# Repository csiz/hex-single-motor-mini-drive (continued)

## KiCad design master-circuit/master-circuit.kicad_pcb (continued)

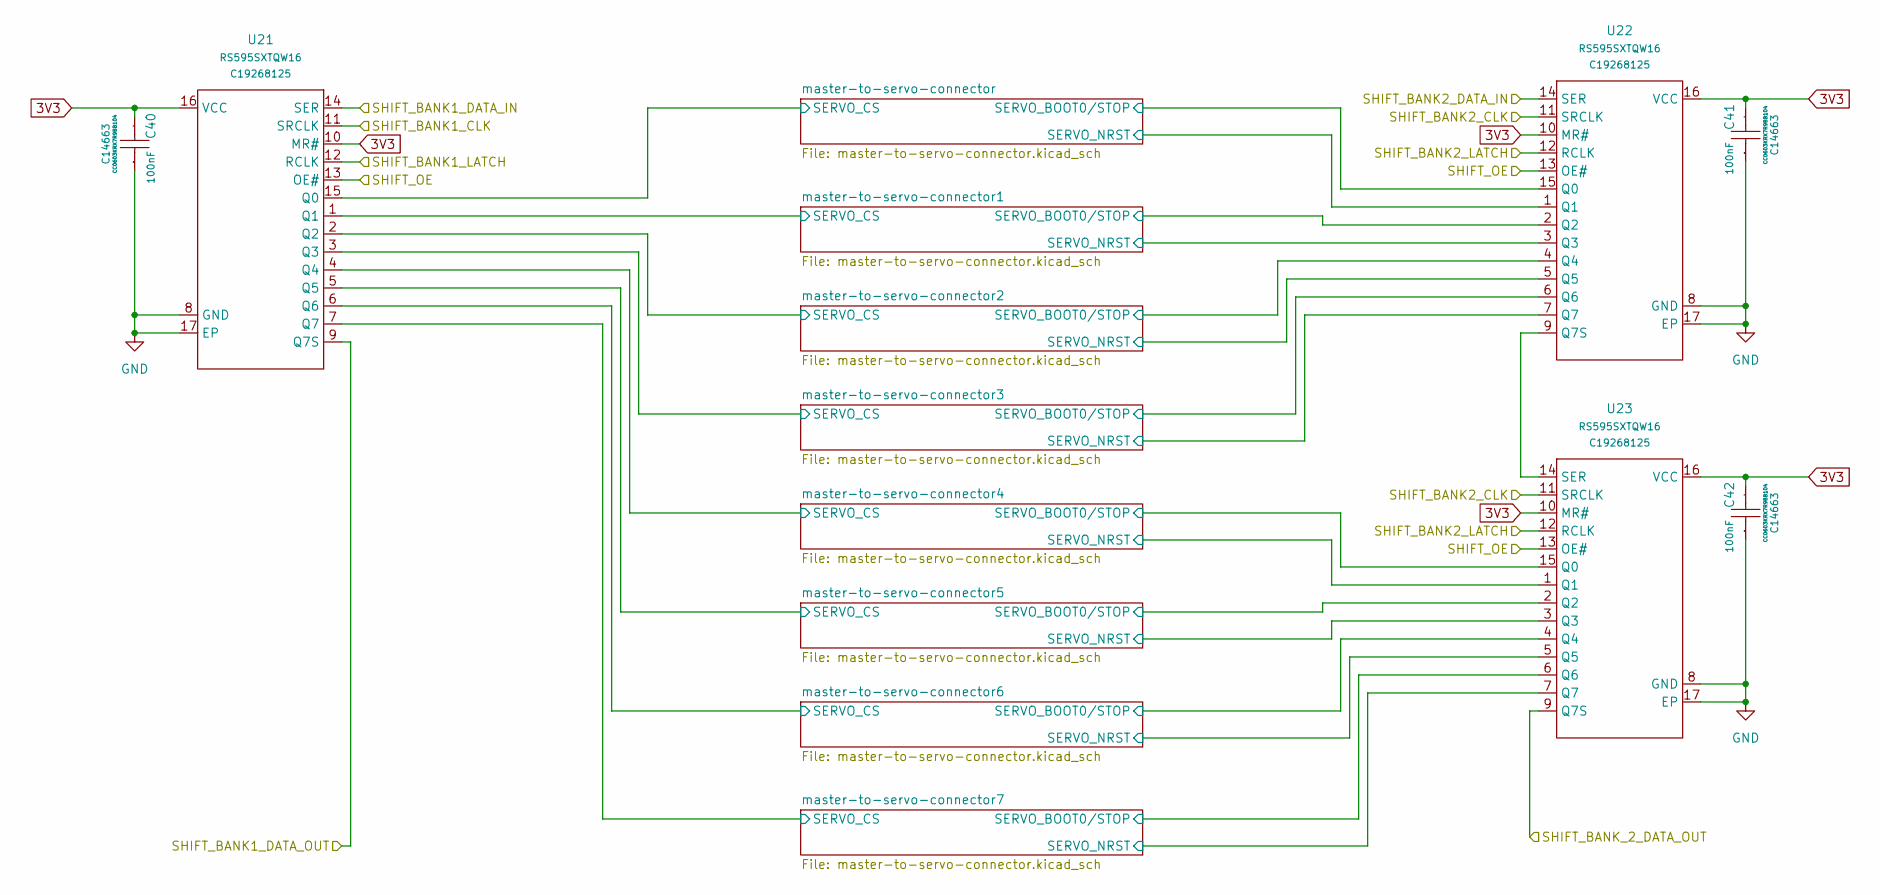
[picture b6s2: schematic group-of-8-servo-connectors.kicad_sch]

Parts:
C40, C41, C42: 100nF; C0603; Manufacturer Part CC0603KRX7R9BB104; LCSC Part Name 100nF ±10% 50V
U21, U22, U23: DHVQFN-16_L3.5-W2.5-P0.50-BL-EP; Manufacturer Part RS595SXTQW16; LCSC Part Name 逻辑RS595S

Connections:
3V3: C40.2, C41.2, C42.2, U21.10 (MR#), U21.16 (VCC), U22.10 (MR#), U22.16 (VCC), U23.10 (MR#), U23.16 (VCC); also elsewhere on the board
/group-of-8-servo-connectors/SHIFT_BANK1_DATA_OUT: U21.9 (Q7S); also elsewhere on the board
/group-of-8-servo-connectors/SHIFT_BANK_2_DATA_OUT: U23.9 (Q7S); also elsewhere on the board
/group-of-8-servo-connectors/master-to-servo-connector1/SERVO_BOOT0/STOP: U22.2 (Q2); also elsewhere on the board
/group-of-8-servo-connectors/master-to-servo-connector1/SERVO_CS: U21.1 (Q1); also elsewhere on the board
/group-of-8-servo-connectors/master-to-servo-connector1/SERVO_NRST: U22.3 (Q3); also elsewhere on the board
/group-of-8-servo-connectors/master-to-servo-connector2/SERVO_BOOT0/STOP: U22.4 (Q4); also elsewhere on the board
/group-of-8-servo-connectors/master-to-servo-connector2/SERVO_CS: U21.2 (Q2); also elsewhere on the board
/group-of-8-servo-connectors/master-to-servo-connector2/SERVO_NRST: U22.5 (Q5); also elsewhere on the board
/group-of-8-servo-connectors/master-to-servo-connector3/SERVO_BOOT0/STOP: U22.6 (Q6); also elsewhere on the board
/group-of-8-servo-connectors/master-to-servo-connector3/SERVO_CS: U21.3 (Q3); also elsewhere on the board
/group-of-8-servo-connectors/master-to-servo-connector3/SERVO_NRST: U22.7 (Q7); also elsewhere on the board
/group-of-8-servo-connectors/master-to-servo-connector4/SERVO_BOOT0/STOP: U23.15 (Q0); also elsewhere on the board
/group-of-8-servo-connectors/master-to-servo-connector4/SERVO_CS: U21.4 (Q4); also elsewhere on the board
/group-of-8-servo-connectors/master-to-servo-connector4/SERVO_NRST: U23.1 (Q1); also elsewhere on the board
/group-of-8-servo-connectors/master-to-servo-connector5/SERVO_BOOT0/STOP: U23.2 (Q2); also elsewhere on the board
/group-of-8-servo-connectors/master-to-servo-connector5/SERVO_CS: U21.5 (Q5); also elsewhere on the board
/group-of-8-servo-connectors/master-to-servo-connector5/SERVO_NRST: U23.3 (Q3); also elsewhere on the board
/group-of-8-servo-connectors/master-to-servo-connector6/SERVO_BOOT0/STOP: U23.4 (Q4); also elsewhere on the board
/group-of-8-servo-connectors/master-to-servo-connector6/SERVO_CS: U21.6 (Q6); also elsewhere on the board
/group-of-8-servo-connectors/master-to-servo-connector6/SERVO_NRST: U23.5 (Q5); also elsewhere on the board
/group-of-8-servo-connectors/master-to-servo-connector7/SERVO_BOOT0/STOP: U23.6 (Q6); also elsewhere on the board
/group-of-8-servo-connectors/master-to-servo-connector7/SERVO_CS: U21.7 (Q7); also elsewhere on the board
/group-of-8-servo-connectors/master-to-servo-connector7/SERVO_NRST: U23.7 (Q7); also elsewhere on the board
/group-of-8-servo-connectors/master-to-servo-connector/SERVO_BOOT0/STOP: U22.15 (Q0); also elsewhere on the board
/group-of-8-servo-connectors/master-to-servo-connector/SERVO_CS: U21.15 (Q0); also elsewhere on the board
/group-of-8-servo-connectors/master-to-servo-connector/SERVO_NRST: U22.1 (Q1); also elsewhere on the board
FSPICLK/SPI2_CLK: U22.11 (SRCLK), U23.11 (SRCLK); also elsewhere on the board
FSPID/SPI2_MOSI: U22.14 (SER); also elsewhere on the board
GND: C40.1, C41.1, C42.1, U21.8 (GND), U21.17 (EP), U22.8 (GND), U22.17 (EP), U23.8 (GND), U23.17 (EP); also elsewhere on the board
unnamed: U22.9 (Q7S), U23.14 (SER)
SHIFT_BANK1_LATCH: U21.12 (RCLK); also elsewhere on the board
SHIFT_BANK2_LATCH: U22.12 (RCLK), U23.12 (RCLK); also elsewhere on the board
SHIFT_OE: U21.13 (OE#), U22.13 (OE#), U23.13 (OE#); also elsewhere on the board
SPI3_CLK: U21.11 (SRCLK); also elsewhere on the board
SPI3_MOSI: U21.14 (SER); also elsewhere on the board

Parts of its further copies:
C43, C44, C45, C46, C47, C48: 100nF; C0603; Manufacturer Part CC0603KRX7R9BB104; LCSC Part Name 100nF ±10% 50V
U24, U25, U26, U27, U28, U29: DHVQFN-16_L3.5-W2.5-P0.50-BL-EP; Manufacturer Part RS595SXTQW16; LCSC Part Name 逻辑RS595S

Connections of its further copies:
3V3: C43.2, C44.2, C45.2, C46.2, C47.2, C48.2, U24.10 (MR#), U24.16 (VCC), U25.10 (MR#), U25.16 (VCC), U26.10 (MR#), U26.16 (VCC), U27.10 (MR#), U27.16 (VCC), U28.10 (MR#), U28.16 (VCC), U29.10 (MR#), U29.16 (VCC); also elsewhere on the board
/group-of-8-servo-connectors1/SHIFT_BANK1_DATA_OUT: U24.9 (Q7S), U27.14 (SER)
/group-of-8-servo-connectors1/SHIFT_BANK_2_DATA_OUT: U26.9 (Q7S), U28.14 (SER)
/group-of-8-servo-connectors1/master-to-servo-connector1/SERVO_BOOT0/STOP: U25.2 (Q2); also elsewhere on the board
/group-of-8-servo-connectors1/master-to-servo-connector1/SERVO_CS: U24.1 (Q1); also elsewhere on the board
/group-of-8-servo-connectors1/master-to-servo-connector1/SERVO_NRST: U25.3 (Q3); also elsewhere on the board
/group-of-8-servo-connectors1/master-to-servo-connector2/SERVO_BOOT0/STOP: U25.4 (Q4); also elsewhere on the board
/group-of-8-servo-connectors1/master-to-servo-connector2/SERVO_CS: U24.2 (Q2); also elsewhere on the board
/group-of-8-servo-connectors1/master-to-servo-connector2/SERVO_NRST: U25.5 (Q5); also elsewhere on the board
/group-of-8-servo-connectors1/master-to-servo-connector3/SERVO_BOOT0/STOP: U25.6 (Q6); also elsewhere on the board
/group-of-8-servo-connectors1/master-to-servo-connector3/SERVO_CS: U24.3 (Q3); also elsewhere on the board
/group-of-8-servo-connectors1/master-to-servo-connector3/SERVO_NRST: U25.7 (Q7); also elsewhere on the board
/group-of-8-servo-connectors1/master-to-servo-connector4/SERVO_BOOT0/STOP: U26.15 (Q0); also elsewhere on the board
/group-of-8-servo-connectors1/master-to-servo-connector4/SERVO_CS: U24.4 (Q4); also elsewhere on the board
/group-of-8-servo-connectors1/master-to-servo-connector4/SERVO_NRST: U26.1 (Q1); also elsewhere on the board
/group-of-8-servo-connectors1/master-to-servo-connector5/SERVO_BOOT0/STOP: U26.2 (Q2); also elsewhere on the board
/group-of-8-servo-connectors1/master-to-servo-connector5/SERVO_CS: U24.5 (Q5); also elsewhere on the board
/group-of-8-servo-connectors1/master-to-servo-connector5/SERVO_NRST: U26.3 (Q3); also elsewhere on the board
/group-of-8-servo-connectors1/master-to-servo-connector6/SERVO_BOOT0/STOP: U26.4 (Q4); also elsewhere on the board
/group-of-8-servo-connectors1/master-to-servo-connector6/SERVO_CS: U24.6 (Q6); also elsewhere on the board
/group-of-8-servo-connectors1/master-to-servo-connector6/SERVO_NRST: U26.5 (Q5); also elsewhere on the board
/group-of-8-servo-connectors1/master-to-servo-connector7/SERVO_BOOT0/STOP: U26.6 (Q6); also elsewhere on the board
/group-of-8-servo-connectors1/master-to-servo-connector7/SERVO_CS: U24.7 (Q7); also elsewhere on the board
/group-of-8-servo-connectors1/master-to-servo-connector7/SERVO_NRST: U26.7 (Q7); also elsewhere on the board
/group-of-8-servo-connectors1/master-to-servo-connector/SERVO_BOOT0/STOP: U25.15 (Q0); also elsewhere on the board
/group-of-8-servo-connectors1/master-to-servo-connector/SERVO_CS: U24.15 (Q0); also elsewhere on the board
/group-of-8-servo-connectors1/master-to-servo-connector/SERVO_NRST: U25.1 (Q1); also elsewhere on the board
/group-of-8-servo-connectors2/SHIFT_BANK1_DATA_OUT: U27.9 (Q7S)
/group-of-8-servo-connectors2/master-to-servo-connector1/SERVO_BOOT0/STOP: U28.2 (Q2); also elsewhere on the board
/group-of-8-servo-connectors2/master-to-servo-connector1/SERVO_CS: U27.1 (Q1); also elsewhere on the board
/group-of-8-servo-connectors2/master-to-servo-connector1/SERVO_NRST: U28.3 (Q3); also elsewhere on the board
/group-of-8-servo-connectors2/master-to-servo-connector2/SERVO_BOOT0/STOP: U28.4 (Q4); also elsewhere on the board
/group-of-8-servo-connectors2/master-to-servo-connector2/SERVO_CS: U27.2 (Q2); also elsewhere on the board
/group-of-8-servo-connectors2/master-to-servo-connector2/SERVO_NRST: U28.5 (Q5); also elsewhere on the board
/group-of-8-servo-connectors2/master-to-servo-connector3/SERVO_BOOT0/STOP: U28.6 (Q6); also elsewhere on the board
/group-of-8-servo-connectors2/master-to-servo-connector3/SERVO_CS: U27.3 (Q3); also elsewhere on the board
/group-of-8-servo-connectors2/master-to-servo-connector3/SERVO_NRST: U28.7 (Q7); also elsewhere on the board
/group-of-8-servo-connectors2/master-to-servo-connector4/SERVO_BOOT0/STOP: U29.15 (Q0); also elsewhere on the board
/group-of-8-servo-connectors2/master-to-servo-connector4/SERVO_CS: U27.4 (Q4); also elsewhere on the board
/group-of-8-servo-connectors2/master-to-servo-connector4/SERVO_NRST: U29.1 (Q1); also elsewhere on the board
/group-of-8-servo-connectors2/master-to-servo-connector5/SERVO_BOOT0/STOP: U29.2 (Q2); also elsewhere on the board
/group-of-8-servo-connectors2/master-to-servo-connector5/SERVO_CS: U27.5 (Q5); also elsewhere on the board
/group-of-8-servo-connectors2/master-to-servo-connector5/SERVO_NRST: U29.3 (Q3); also elsewhere on the board
/group-of-8-servo-connectors2/master-to-servo-connector6/SERVO_BOOT0/STOP: U29.4 (Q4); also elsewhere on the board
/group-of-8-servo-connectors2/master-to-servo-connector6/SERVO_CS: U27.6 (Q6); also elsewhere on the board
/group-of-8-servo-connectors2/master-to-servo-connector6/SERVO_NRST: U29.5 (Q5); also elsewhere on the board
/group-of-8-servo-connectors2/master-to-servo-connector7/SERVO_BOOT0/STOP: U29.6 (Q6); also elsewhere on the board
/group-of-8-servo-connectors2/master-to-servo-connector7/SERVO_CS: U27.7 (Q7); also elsewhere on the board
/group-of-8-servo-connectors2/master-to-servo-connector7/SERVO_NRST: U29.7 (Q7); also elsewhere on the board
/group-of-8-servo-connectors2/master-to-servo-connector/SERVO_BOOT0/STOP: U28.15 (Q0); also elsewhere on the board
/group-of-8-servo-connectors2/master-to-servo-connector/SERVO_CS: U27.15 (Q0); also elsewhere on the board
/group-of-8-servo-connectors2/master-to-servo-connector/SERVO_NRST: U28.1 (Q1); also elsewhere on the board
/group-of-8-servo-connectors/SHIFT_BANK1_DATA_OUT: U24.14 (SER); also elsewhere on the board
/group-of-8-servo-connectors/SHIFT_BANK_2_DATA_OUT: U25.14 (SER); also elsewhere on the board
FSPICLK/SPI2_CLK: U25.11 (SRCLK), U26.11 (SRCLK), U28.11 (SRCLK), U29.11 (SRCLK); also elsewhere on the board
GND: C43.1, C44.1, C45.1, C46.1, C47.1, C48.1, U24.8 (GND), U24.17 (EP), U25.8 (GND), U25.17 (EP), U26.8 (GND), U26.17 (EP), U27.8 (GND), U27.17 (EP), U28.8 (GND), U28.17 (EP), U29.8 (GND), U29.17 (EP); also elsewhere on the board
unnamed: U25.9 (Q7S), U26.14 (SER)
unnamed: U28.9 (Q7S), U29.14 (SER)
SHIFT_BANK1_LATCH: U24.12 (RCLK), U27.12 (RCLK); also elsewhere on the board
SHIFT_BANK2_LATCH: U25.12 (RCLK), U26.12 (RCLK), U28.12 (RCLK), U29.12 (RCLK); also elsewhere on the board
SHIFT_BANK_2_DATA_CONT: U29.9 (Q7S); also elsewhere on the board
SHIFT_OE: U24.13 (OE#), U25.13 (OE#), U26.13 (OE#), U27.13 (OE#), U28.13 (OE#), U29.13 (OE#); also elsewhere on the board
SPI3_CLK: U24.11 (SRCLK), U27.11 (SRCLK); also elsewhere on the board

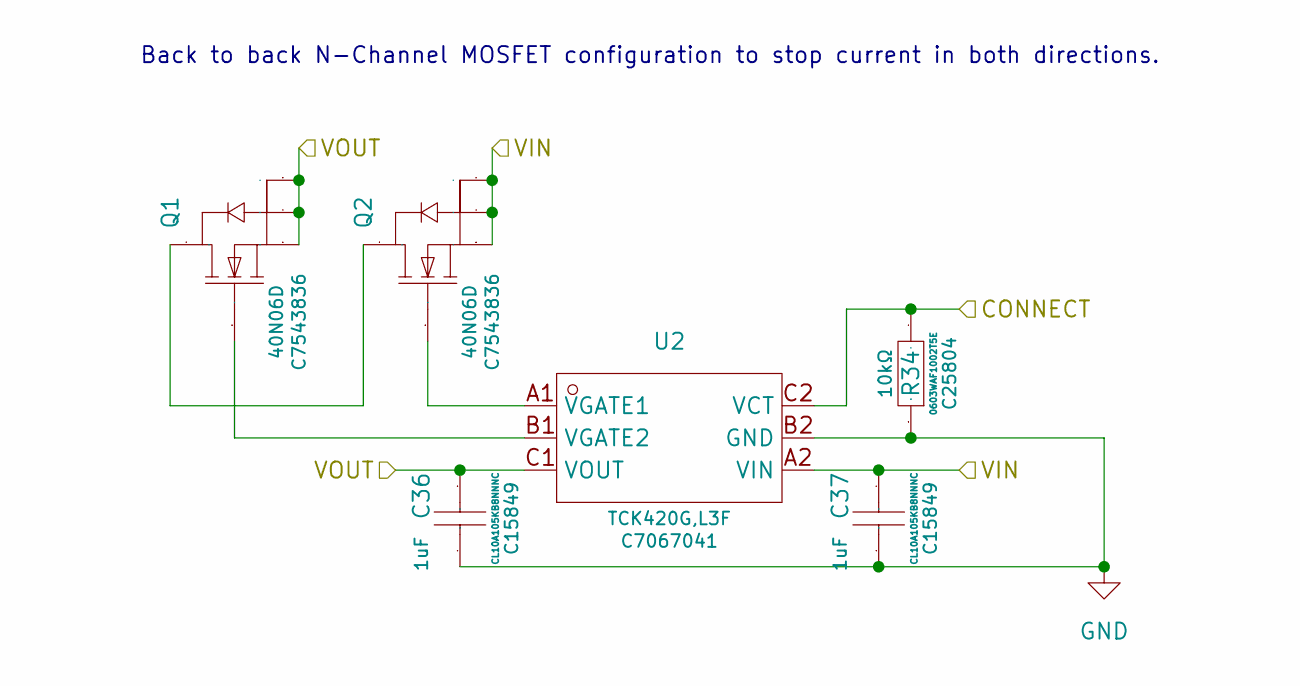
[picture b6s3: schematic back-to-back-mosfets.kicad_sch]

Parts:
C36, C37: 1uF; C0603; Manufacturer Part CL10A105KB8NNNC; LCSC Part Name 1uF ±10% 50V
Q1, Q2: WDFN-5_L3.1-W3.1-P0.65-BL_1; Manufacturer Part 40N06D; LCSC Part Name 1个N沟道 耐压:60V 电流:40A
R34: 10kΩ; R0603; Manufacturer Part 0603WAF1002T5E; LCSC Part Name 厚膜电阻 10kΩ ±1% 100mW
U2: WLCSP-6_L1.2-W0.8-P0.40-TL; Manufacturer Part TCK420G,L3F; LCSC Part Name 过压保护MOSFET栅极驱动IC

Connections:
CONNECT_BATTERY: R34.2, U2.C2 (VCT); also elsewhere on the board
GND: C36.1, C37.1, R34.1, U2.B2 (GND); also elsewhere on the board
unnamed: Q1.5 (D), Q2.5 (D)
unnamed: Q1.4 (G), U2.B1 (VGATE2)
unnamed: Q2.4 (G), U2.A1 (VGATE1)
VBATTERY: C37.2, Q2.1 (S), Q2.2 (S), Q2.3 (S), U2.A2 (VIN); also elsewhere on the board
VCC: C36.2, Q1.1 (S), Q1.2 (S), Q1.3 (S), U2.C1 (VOUT); also elsewhere on the board

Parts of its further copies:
C29, C38, C39, C49, C50, C51: 1uF; C0603; Manufacturer Part CL10A105KB8NNNC; LCSC Part Name 1uF ±10% 50V
Q3, Q4, Q5, Q6, Q7, Q8: WDFN-5_L3.1-W3.1-P0.65-BL_1; Manufacturer Part 40N06D; LCSC Part Name 1个N沟道 耐压:60V 电流:40A
R35, R36, R37: 10kΩ; R0603; Manufacturer Part 0603WAF1002T5E; LCSC Part Name 厚膜电阻 10kΩ ±1% 100mW
U7, U12, U13: WLCSP-6_L1.2-W0.8-P0.40-TL; Manufacturer Part TCK420G,L3F; LCSC Part Name 过压保护MOSFET栅极驱动IC

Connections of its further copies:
5V: C51.2, Q8.1 (S), Q8.2 (S), Q8.3 (S), U13.A2 (VIN); also elsewhere on the board
CONNECT_SENSORS_5V: R37.2, U13.C2 (VCT); also elsewhere on the board
CONNECT_SENSORS_VCC: R35.2, U7.C2 (VCT); also elsewhere on the board
CONNECT_VBUS: R36.2, U12.C2 (VCT); also elsewhere on the board
GND: C29.1, C38.1, C39.1, C49.1, C50.1, C51.1, R35.1, R36.1, R37.1, U7.B2 (GND), U12.B2 (GND), U13.B2 (GND); also elsewhere on the board
unnamed: Q3.5 (D), Q4.5 (D)
unnamed: Q3.4 (G), U7.B1 (VGATE2)
unnamed: Q4.4 (G), U7.A1 (VGATE1)
unnamed: Q5.5 (D), Q6.5 (D)
unnamed: Q5.4 (G), U12.B1 (VGATE2)
unnamed: Q6.4 (G), U12.A1 (VGATE1)
unnamed: Q7.5 (D), Q8.5 (D)
unnamed: Q7.4 (G), U13.B1 (VGATE2)
unnamed: Q8.4 (G), U13.A1 (VGATE1)
SENSORS_VBUS: C38.2, C50.2, Q3.1 (S), Q3.2 (S), Q3.3 (S), Q7.1 (S), Q7.2 (S), Q7.3 (S), U7.C1 (VOUT), U13.C1 (VOUT); also elsewhere on the board
VBUS: C49.2, Q6.1 (S), Q6.2 (S), Q6.3 (S), U12.A2 (VIN); also elsewhere on the board
VCC: C29.2, C39.2, Q4.1 (S), Q4.2 (S), Q4.3 (S), Q5.1 (S), Q5.2 (S), Q5.3 (S), U7.A2 (VIN), U12.C1 (VOUT); also elsewhere on the board

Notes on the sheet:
Back to back N-Channel MOSFET configuration to stop current in both directions.

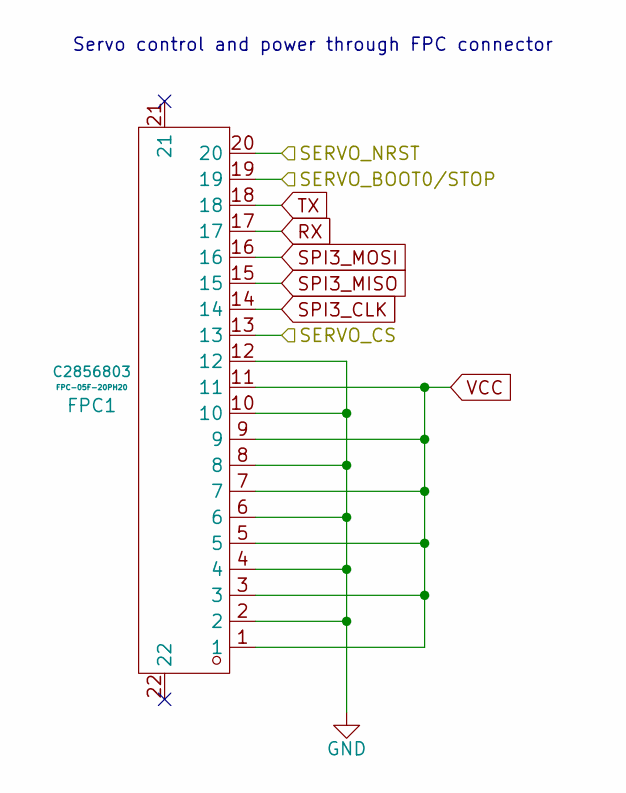
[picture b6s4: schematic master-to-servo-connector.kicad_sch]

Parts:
FPC1: FPC-SMD_20P-P0.50_XUNPU_FPC-05F-20PH20; Manufacturer Part FPC-05F-20PH20; LCSC Part Name 翻盖式 卧贴 P数:20P 间距:0.5mm

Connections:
/group-of-8-servo-connectors/master-to-servo-connector/SERVO_BOOT0/STOP: FPC1.19; also elsewhere on the board
/group-of-8-servo-connectors/master-to-servo-connector/SERVO_CS: FPC1.13; also elsewhere on the board
/group-of-8-servo-connectors/master-to-servo-connector/SERVO_NRST: FPC1.20; also elsewhere on the board
GND: FPC1.2, FPC1.4, FPC1.6, FPC1.8, FPC1.10, FPC1.12; also elsewhere on the board
RX: FPC1.17; also elsewhere on the board
SPI3_CLK: FPC1.14; also elsewhere on the board
SPI3_MISO: FPC1.15; also elsewhere on the board
SPI3_MOSI: FPC1.16; also elsewhere on the board
TX: FPC1.18; also elsewhere on the board
VCC: FPC1.1, FPC1.3, FPC1.5, FPC1.7, FPC1.9, FPC1.11; also elsewhere on the board

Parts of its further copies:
FPC2, FPC3, FPC4, FPC5, FPC6, FPC7, FPC8, FPC9, FPC10, FPC11, FPC12, FPC13, FPC14, FPC15, FPC16, FPC17, FPC18, FPC19, FPC20, FPC21, FPC22, FPC23, FPC24: FPC-SMD_20P-P0.50_XUNPU_FPC-05F-20PH20; Manufacturer Part FPC-05F-20PH20; LCSC Part Name 翻盖式 卧贴 P数:20P 间距:0.5mm

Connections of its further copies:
/group-of-8-servo-connectors1/master-to-servo-connector1/SERVO_BOOT0/STOP: FPC10.19; also elsewhere on the board
/group-of-8-servo-connectors1/master-to-servo-connector1/SERVO_CS: FPC10.13; also elsewhere on the board
/group-of-8-servo-connectors1/master-to-servo-connector1/SERVO_NRST: FPC10.20; also elsewhere on the board
/group-of-8-servo-connectors1/master-to-servo-connector2/SERVO_BOOT0/STOP: FPC11.19; also elsewhere on the board
/group-of-8-servo-connectors1/master-to-servo-connector2/SERVO_CS: FPC11.13; also elsewhere on the board
/group-of-8-servo-connectors1/master-to-servo-connector2/SERVO_NRST: FPC11.20; also elsewhere on the board
/group-of-8-servo-connectors1/master-to-servo-connector3/SERVO_BOOT0/STOP: FPC12.19; also elsewhere on the board
/group-of-8-servo-connectors1/master-to-servo-connector3/SERVO_CS: FPC12.13; also elsewhere on the board
/group-of-8-servo-connectors1/master-to-servo-connector3/SERVO_NRST: FPC12.20; also elsewhere on the board
/group-of-8-servo-connectors1/master-to-servo-connector4/SERVO_BOOT0/STOP: FPC13.19; also elsewhere on the board
/group-of-8-servo-connectors1/master-to-servo-connector4/SERVO_CS: FPC13.13; also elsewhere on the board
/group-of-8-servo-connectors1/master-to-servo-connector4/SERVO_NRST: FPC13.20; also elsewhere on the board
/group-of-8-servo-connectors1/master-to-servo-connector5/SERVO_BOOT0/STOP: FPC14.19; also elsewhere on the board
/group-of-8-servo-connectors1/master-to-servo-connector5/SERVO_CS: FPC14.13; also elsewhere on the board
/group-of-8-servo-connectors1/master-to-servo-connector5/SERVO_NRST: FPC14.20; also elsewhere on the board
/group-of-8-servo-connectors1/master-to-servo-connector6/SERVO_BOOT0/STOP: FPC15.19; also elsewhere on the board
/group-of-8-servo-connectors1/master-to-servo-connector6/SERVO_CS: FPC15.13; also elsewhere on the board
/group-of-8-servo-connectors1/master-to-servo-connector6/SERVO_NRST: FPC15.20; also elsewhere on the board
/group-of-8-servo-connectors1/master-to-servo-connector7/SERVO_BOOT0/STOP: FPC16.19; also elsewhere on the board
/group-of-8-servo-connectors1/master-to-servo-connector7/SERVO_CS: FPC16.13; also elsewhere on the board
/group-of-8-servo-connectors1/master-to-servo-connector7/SERVO_NRST: FPC16.20; also elsewhere on the board
/group-of-8-servo-connectors1/master-to-servo-connector/SERVO_BOOT0/STOP: FPC9.19; also elsewhere on the board
/group-of-8-servo-connectors1/master-to-servo-connector/SERVO_CS: FPC9.13; also elsewhere on the board
/group-of-8-servo-connectors1/master-to-servo-connector/SERVO_NRST: FPC9.20; also elsewhere on the board
/group-of-8-servo-connectors2/master-to-servo-connector1/SERVO_BOOT0/STOP: FPC18.19; also elsewhere on the board
/group-of-8-servo-connectors2/master-to-servo-connector1/SERVO_CS: FPC18.13; also elsewhere on the board
/group-of-8-servo-connectors2/master-to-servo-connector1/SERVO_NRST: FPC18.20; also elsewhere on the board
/group-of-8-servo-connectors2/master-to-servo-connector2/SERVO_BOOT0/STOP: FPC19.19; also elsewhere on the board
/group-of-8-servo-connectors2/master-to-servo-connector2/SERVO_CS: FPC19.13; also elsewhere on the board
/group-of-8-servo-connectors2/master-to-servo-connector2/SERVO_NRST: FPC19.20; also elsewhere on the board
/group-of-8-servo-connectors2/master-to-servo-connector3/SERVO_BOOT0/STOP: FPC20.19; also elsewhere on the board
/group-of-8-servo-connectors2/master-to-servo-connector3/SERVO_CS: FPC20.13; also elsewhere on the board
/group-of-8-servo-connectors2/master-to-servo-connector3/SERVO_NRST: FPC20.20; also elsewhere on the board
/group-of-8-servo-connectors2/master-to-servo-connector4/SERVO_BOOT0/STOP: FPC21.19; also elsewhere on the board
/group-of-8-servo-connectors2/master-to-servo-connector4/SERVO_CS: FPC21.13; also elsewhere on the board
/group-of-8-servo-connectors2/master-to-servo-connector4/SERVO_NRST: FPC21.20; also elsewhere on the board
/group-of-8-servo-connectors2/master-to-servo-connector5/SERVO_BOOT0/STOP: FPC22.19; also elsewhere on the board
/group-of-8-servo-connectors2/master-to-servo-connector5/SERVO_CS: FPC22.13; also elsewhere on the board
/group-of-8-servo-connectors2/master-to-servo-connector5/SERVO_NRST: FPC22.20; also elsewhere on the board
/group-of-8-servo-connectors2/master-to-servo-connector6/SERVO_BOOT0/STOP: FPC23.19; also elsewhere on the board
/group-of-8-servo-connectors2/master-to-servo-connector6/SERVO_CS: FPC23.13; also elsewhere on the board
/group-of-8-servo-connectors2/master-to-servo-connector6/SERVO_NRST: FPC23.20; also elsewhere on the board
/group-of-8-servo-connectors2/master-to-servo-connector7/SERVO_BOOT0/STOP: FPC24.19; also elsewhere on the board
/group-of-8-servo-connectors2/master-to-servo-connector7/SERVO_CS: FPC24.13; also elsewhere on the board
/group-of-8-servo-connectors2/master-to-servo-connector7/SERVO_NRST: FPC24.20; also elsewhere on the board
/group-of-8-servo-connectors2/master-to-servo-connector/SERVO_BOOT0/STOP: FPC17.19; also elsewhere on the board
/group-of-8-servo-connectors2/master-to-servo-connector/SERVO_CS: FPC17.13; also elsewhere on the board
/group-of-8-servo-connectors2/master-to-servo-connector/SERVO_NRST: FPC17.20; also elsewhere on the board
/group-of-8-servo-connectors/master-to-servo-connector1/SERVO_BOOT0/STOP: FPC2.19; also elsewhere on the board
/group-of-8-servo-connectors/master-to-servo-connector1/SERVO_CS: FPC2.13; also elsewhere on the board
/group-of-8-servo-connectors/master-to-servo-connector1/SERVO_NRST: FPC2.20; also elsewhere on the board
/group-of-8-servo-connectors/master-to-servo-connector2/SERVO_BOOT0/STOP: FPC3.19; also elsewhere on the board
/group-of-8-servo-connectors/master-to-servo-connector2/SERVO_CS: FPC3.13; also elsewhere on the board
/group-of-8-servo-connectors/master-to-servo-connector2/SERVO_NRST: FPC3.20; also elsewhere on the board
/group-of-8-servo-connectors/master-to-servo-connector3/SERVO_BOOT0/STOP: FPC4.19; also elsewhere on the board
/group-of-8-servo-connectors/master-to-servo-connector3/SERVO_CS: FPC4.13; also elsewhere on the board
/group-of-8-servo-connectors/master-to-servo-connector3/SERVO_NRST: FPC4.20; also elsewhere on the board
/group-of-8-servo-connectors/master-to-servo-connector4/SERVO_BOOT0/STOP: FPC5.19; also elsewhere on the board
/group-of-8-servo-connectors/master-to-servo-connector4/SERVO_CS: FPC5.13; also elsewhere on the board
/group-of-8-servo-connectors/master-to-servo-connector4/SERVO_NRST: FPC5.20; also elsewhere on the board
/group-of-8-servo-connectors/master-to-servo-connector5/SERVO_BOOT0/STOP: FPC6.19; also elsewhere on the board
/group-of-8-servo-connectors/master-to-servo-connector5/SERVO_CS: FPC6.13; also elsewhere on the board
/group-of-8-servo-connectors/master-to-servo-connector5/SERVO_NRST: FPC6.20; also elsewhere on the board
/group-of-8-servo-connectors/master-to-servo-connector6/SERVO_BOOT0/STOP: FPC7.19; also elsewhere on the board
/group-of-8-servo-connectors/master-to-servo-connector6/SERVO_CS: FPC7.13; also elsewhere on the board
/group-of-8-servo-connectors/master-to-servo-connector6/SERVO_NRST: FPC7.20; also elsewhere on the board
/group-of-8-servo-connectors/master-to-servo-connector7/SERVO_BOOT0/STOP: FPC8.19; also elsewhere on the board
/group-of-8-servo-connectors/master-to-servo-connector7/SERVO_CS: FPC8.13; also elsewhere on the board
/group-of-8-servo-connectors/master-to-servo-connector7/SERVO_NRST: FPC8.20; also elsewhere on the board
GND: FPC2.2, FPC2.4, FPC2.6, FPC2.8, FPC2.10, FPC2.12, FPC3.2, FPC3.4, FPC3.6, FPC3.8, FPC3.10, FPC3.12, FPC4.2, FPC4.4, FPC4.6, FPC4.8, FPC4.10, FPC4.12, FPC5.2, FPC5.4, FPC5.6, FPC5.8, FPC5.10, FPC5.12, FPC6.2, FPC6.4, FPC6.6, FPC6.8, FPC6.10, FPC6.12, FPC7.2, FPC7.4, FPC7.6, FPC7.8, FPC7.10, FPC7.12, FPC8.2, FPC8.4, FPC8.6, FPC8.8, FPC8.10, FPC8.12, FPC9.2, FPC9.4, FPC9.6, FPC9.8, FPC9.10, FPC9.12, FPC10.2, FPC10.4, FPC10.6, FPC10.8, FPC10.10, FPC10.12, FPC11.2, FPC11.4, FPC11.6, FPC11.8, FPC11.10, FPC11.12, FPC12.2, FPC12.4, FPC12.6, FPC12.8, FPC12.10, FPC12.12, FPC13.2, FPC13.4, FPC13.6, FPC13.8, FPC13.10, FPC13.12, FPC14.2, FPC14.4, FPC14.6, FPC14.8, FPC14.10, FPC14.12, FPC15.2, FPC15.4, FPC15.6, FPC15.8, FPC15.10, FPC15.12, FPC16.2, FPC16.4, FPC16.6, FPC16.8, FPC16.10, FPC16.12, FPC17.2, FPC17.4, FPC17.6, FPC17.8, FPC17.10, FPC17.12, FPC18.2, FPC18.4, FPC18.6, FPC18.8, FPC18.10, FPC18.12, FPC19.2, FPC19.4, FPC19.6, FPC19.8, FPC19.10, FPC19.12, FPC20.2, FPC20.4, FPC20.6, FPC20.8, FPC20.10, FPC20.12, FPC21.2, FPC21.4, FPC21.6, FPC21.8, FPC21.10, FPC21.12, FPC22.2, FPC22.4, FPC22.6, FPC22.8, FPC22.10, FPC22.12, FPC23.2, FPC23.4, FPC23.6, FPC23.8, FPC23.10, FPC23.12, FPC24.2, FPC24.4, FPC24.6, FPC24.8, FPC24.10, FPC24.12; also elsewhere on the board
RX: FPC2.17, FPC3.17, FPC4.17, FPC5.17, FPC6.17, FPC7.17, FPC8.17, FPC9.17, FPC10.17, FPC11.17, FPC12.17, FPC13.17, FPC14.17, FPC15.17, FPC16.17, FPC17.17, FPC18.17, FPC19.17, FPC20.17, FPC21.17, FPC22.17, FPC23.17, FPC24.17; also elsewhere on the board
SPI3_CLK: FPC2.14, FPC3.14, FPC4.14, FPC5.14, FPC6.14, FPC7.14, FPC8.14, FPC9.14, FPC10.14, FPC11.14, FPC12.14, FPC13.14, FPC14.14, FPC15.14, FPC16.14, FPC17.14, FPC18.14, FPC19.14, FPC20.14, FPC21.14, FPC22.14, FPC23.14, FPC24.14; also elsewhere on the board
SPI3_MISO: FPC2.15, FPC3.15, FPC4.15, FPC5.15, FPC6.15, FPC7.15, FPC8.15, FPC9.15, FPC10.15, FPC11.15, FPC12.15, FPC13.15, FPC14.15, FPC15.15, FPC16.15, FPC17.15, FPC18.15, FPC19.15, FPC20.15, FPC21.15, FPC22.15, FPC23.15, FPC24.15; also elsewhere on the board
SPI3_MOSI: FPC2.16, FPC3.16, FPC4.16, FPC5.16, FPC6.16, FPC7.16, FPC8.16, FPC9.16, FPC10.16, FPC11.16, FPC12.16, FPC13.16, FPC14.16, FPC15.16, FPC16.16, FPC17.16, FPC18.16, FPC19.16, FPC20.16, FPC21.16, FPC22.16, FPC23.16, FPC24.16; also elsewhere on the board
TX: FPC2.18, FPC3.18, FPC4.18, FPC5.18, FPC6.18, FPC7.18, FPC8.18, FPC9.18, FPC10.18, FPC11.18, FPC12.18, FPC13.18, FPC14.18, FPC15.18, FPC16.18, FPC17.18, FPC18.18, FPC19.18, FPC20.18, FPC21.18, FPC22.18, FPC23.18, FPC24.18; also elsewhere on the board
VCC: FPC2.1, FPC2.3, FPC2.5, FPC2.7, FPC2.9, FPC2.11, FPC3.1, FPC3.3, FPC3.5, FPC3.7, FPC3.9, FPC3.11, FPC4.1, FPC4.3, FPC4.5, FPC4.7, FPC4.9, FPC4.11, FPC5.1, FPC5.3, FPC5.5, FPC5.7, FPC5.9, FPC5.11, FPC6.1, FPC6.3, FPC6.5, FPC6.7, FPC6.9, FPC6.11, FPC7.1, FPC7.3, FPC7.5, FPC7.7, FPC7.9, FPC7.11, FPC8.1, FPC8.3, FPC8.5, FPC8.7, FPC8.9, FPC8.11, FPC9.1, FPC9.3, FPC9.5, FPC9.7, FPC9.9, FPC9.11, FPC10.1, FPC10.3, FPC10.5, FPC10.7, FPC10.9, FPC10.11, FPC11.1, FPC11.3, FPC11.5, FPC11.7, FPC11.9, FPC11.11, FPC12.1, FPC12.3, FPC12.5, FPC12.7, FPC12.9, FPC12.11, FPC13.1, FPC13.3, FPC13.5, FPC13.7, FPC13.9, FPC13.11, FPC14.1, FPC14.3, FPC14.5, FPC14.7, FPC14.9, FPC14.11, FPC15.1, FPC15.3, FPC15.5, FPC15.7, FPC15.9, FPC15.11, FPC16.1, FPC16.3, FPC16.5, FPC16.7, FPC16.9, FPC16.11, FPC17.1, FPC17.3, FPC17.5, FPC17.7, FPC17.9, FPC17.11, FPC18.1, FPC18.3, FPC18.5, FPC18.7, FPC18.9, FPC18.11, FPC19.1, FPC19.3, FPC19.5, FPC19.7, FPC19.9, FPC19.11, FPC20.1, FPC20.3, FPC20.5, FPC20.7, FPC20.9, FPC20.11, FPC21.1, FPC21.3, FPC21.5, FPC21.7, FPC21.9, FPC21.11, FPC22.1, FPC22.3, FPC22.5, FPC22.7, FPC22.9, FPC22.11, FPC23.1, FPC23.3, FPC23.5, FPC23.7, FPC23.9, FPC23.11, FPC24.1, FPC24.3, FPC24.5, FPC24.7, FPC24.9, FPC24.11; also elsewhere on the board

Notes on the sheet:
Servo control and power through FPC connector

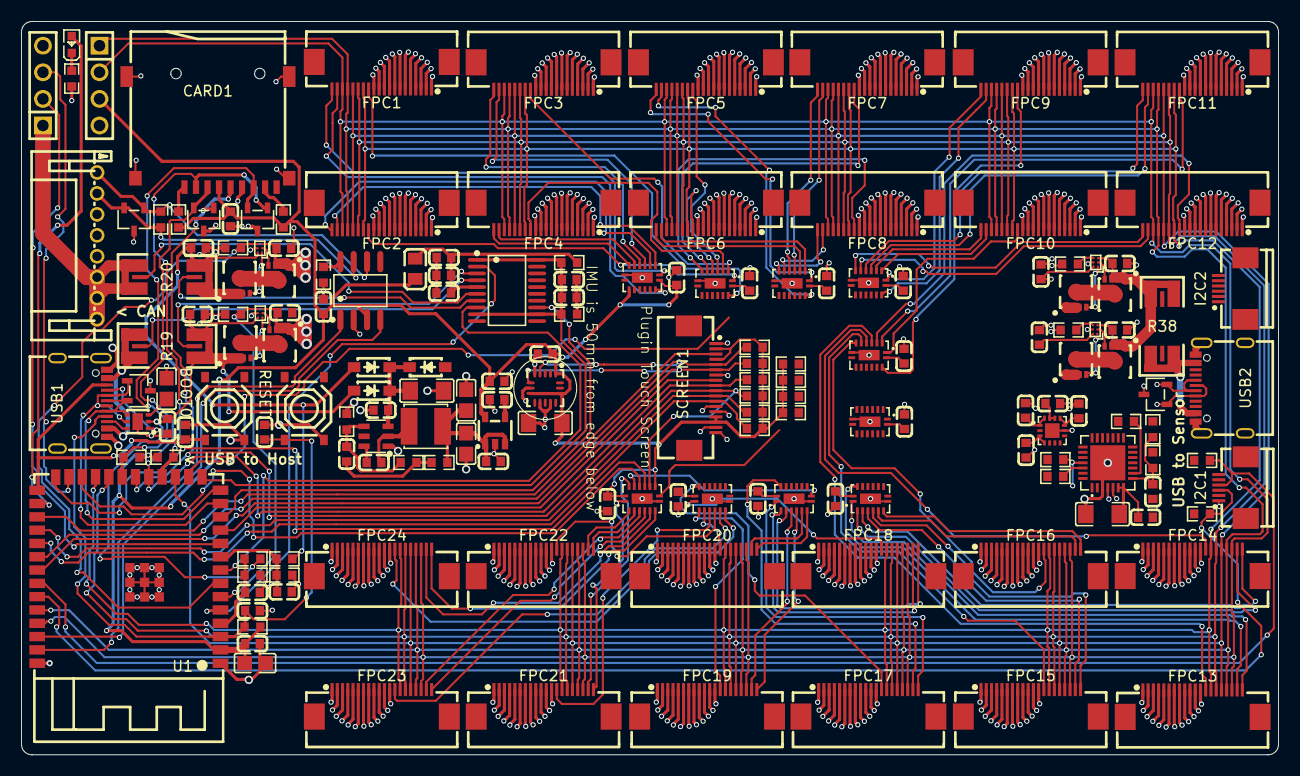
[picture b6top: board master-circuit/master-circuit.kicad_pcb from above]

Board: 4 copper layers, 120.0 x 70.0 mm, 170 parts (0 on the bottom side), 175 nets.

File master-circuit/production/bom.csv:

Designator,Footprint,Quantity,Value,LCSC Part #
"C1, C12, C18, C19, C20, C29, C35, C36, C37, C38, C39, C49, C50, C51, C8",C0603,15,1uF,C15849
"C10, C11",C0603,2,1nF,C1588
"C13, C14, C15, C16, C2, C22, C25, C26, C30, C31, C33, C34, C4, C40, C41, C42, C43, C44, C45, C46, C47, C48, C5, C7",C0603,24,100nF,C14663
"C17, C21, C32",C1206,3,10uF,C13585
"C23, C24, C3",C0805,3,22uF,C45783
"C27, C28",C0603,2,330pF,C1664
C6,C0603,1,100pF,C14858
C9,C0603,1,10nF,C57112
CARD1,TF-SMD_TF-01A,1,~,C91145
"D1, D3, D9",SOD-123_L2.7-W1.6-LS3.7-RD-1,3,~,C8598
"D2, D4, D6, D7, D8",SOT-23-3_L3.0-W1.7-P0.95-LS2.9-BR,5,~,C32677
"FPC1, FPC10, FPC11, FPC12, FPC13, FPC14, FPC15, FPC16, FPC17, FPC18, FPC19, FPC2, FPC20, FPC21, FPC22, FPC23, FPC24, FPC3, FPC4, FPC5, FPC6, FPC7, FPC8, FPC9",FPC-SMD_20P-P0.50_XUNPU_FPC-05F-20PH20,24,~,C2856803
"I2C1, I2C2",FPC-SMD_6P-P0.50_XUNPU_FPC-05F-6PH20,2,~,C2856796
L1,IND-SMD_L4.0-W4.0,1,15uH,C602033
L2,L0805,1,10uH,C1046
LED1,LED0603-RD,1,~,C2286
"Q1, Q2, Q3, Q4, Q5, Q6, Q7, Q8",WDFN-5_L3.1-W3.1-P0.65-BL_1,8,~,C7543836
"R1, R11, R12, R13, R14, R15, R17, R18, R21, R22, R24, R25, R26, R27, R28, R29, R3, R30, R31, R32, R33, R34, R35, R36, R37, R7, R8, R9",R0603,28,10kΩ,C25804
R10,R0603,1,49.9Ω,C23185
R16,R0603,1,120Ω,C22787
"R19, R20, R38",R2512 Shunt with Kelvin connections,3,5mΩ,C393074
"R2, R4, R5",R0603,3,100kΩ,C25803
"R23, R39",R0603,2,1.5kΩ,C22843
R40,R0603,1,20kΩ,C4184
R41,R0603,1,47kΩ,C25819
R6,R0603,1,13kΩ,C22797
SCREEN1,FPC-SMD_18P-P0.50_FPC-05F-18PH20,1,~,C2856802
"SW1, SW2",SW-SMD_4P-L5.1-W5.1-P3.70-LS6.5-TL_H1.5,2,~,C318884
U1,WIRELM-SMD_ESP32-S3-WROOM-1,1,~,C2913202
U10,QFN-28_L5.0-W5.0-P0.50-TL-EP3.3,1,~,C964632
U11,TSSOP-20_L6.5-W4.4-P0.65-LS6.4-BL,1,~,C2058366
"U12, U13, U2, U7",WLCSP-6_L1.2-W0.8-P0.40-TL,4,~,C7067041
U17,SOIC-8_L4.9-W3.9-P1.27-LS6.0-BL,1,~,C12084
U18,LGA-16_L3.0-W3.0-P0.50-TL,1,~,C15134
"U21, U22, U23, U24, U25, U26, U27, U28, U29, U8",DHVQFN-16_L3.5-W2.5-P0.50-BL-EP,10,~,C19268125
U3,SOT-23-5_L3.0-W1.6-P0.95-LS2.8-BL,1,~,C2969807
U4,SOT-23-6_L2.9-W1.6-P0.95-LS2.8-BL,1,~,C191884
U5,TDFN-6_L2.0-W2.0-P0.65-TL-EP,1,~,C22373734
U6,C0805,1,20nF 5%,C1853321
U9,QFN-14_L2.5-W2.5-P0.50-TL-EP1.4,1,~,C7471922
"USB1, USB2",USB-C-SMD_TYPE-C16PIN,2,~,C393939
